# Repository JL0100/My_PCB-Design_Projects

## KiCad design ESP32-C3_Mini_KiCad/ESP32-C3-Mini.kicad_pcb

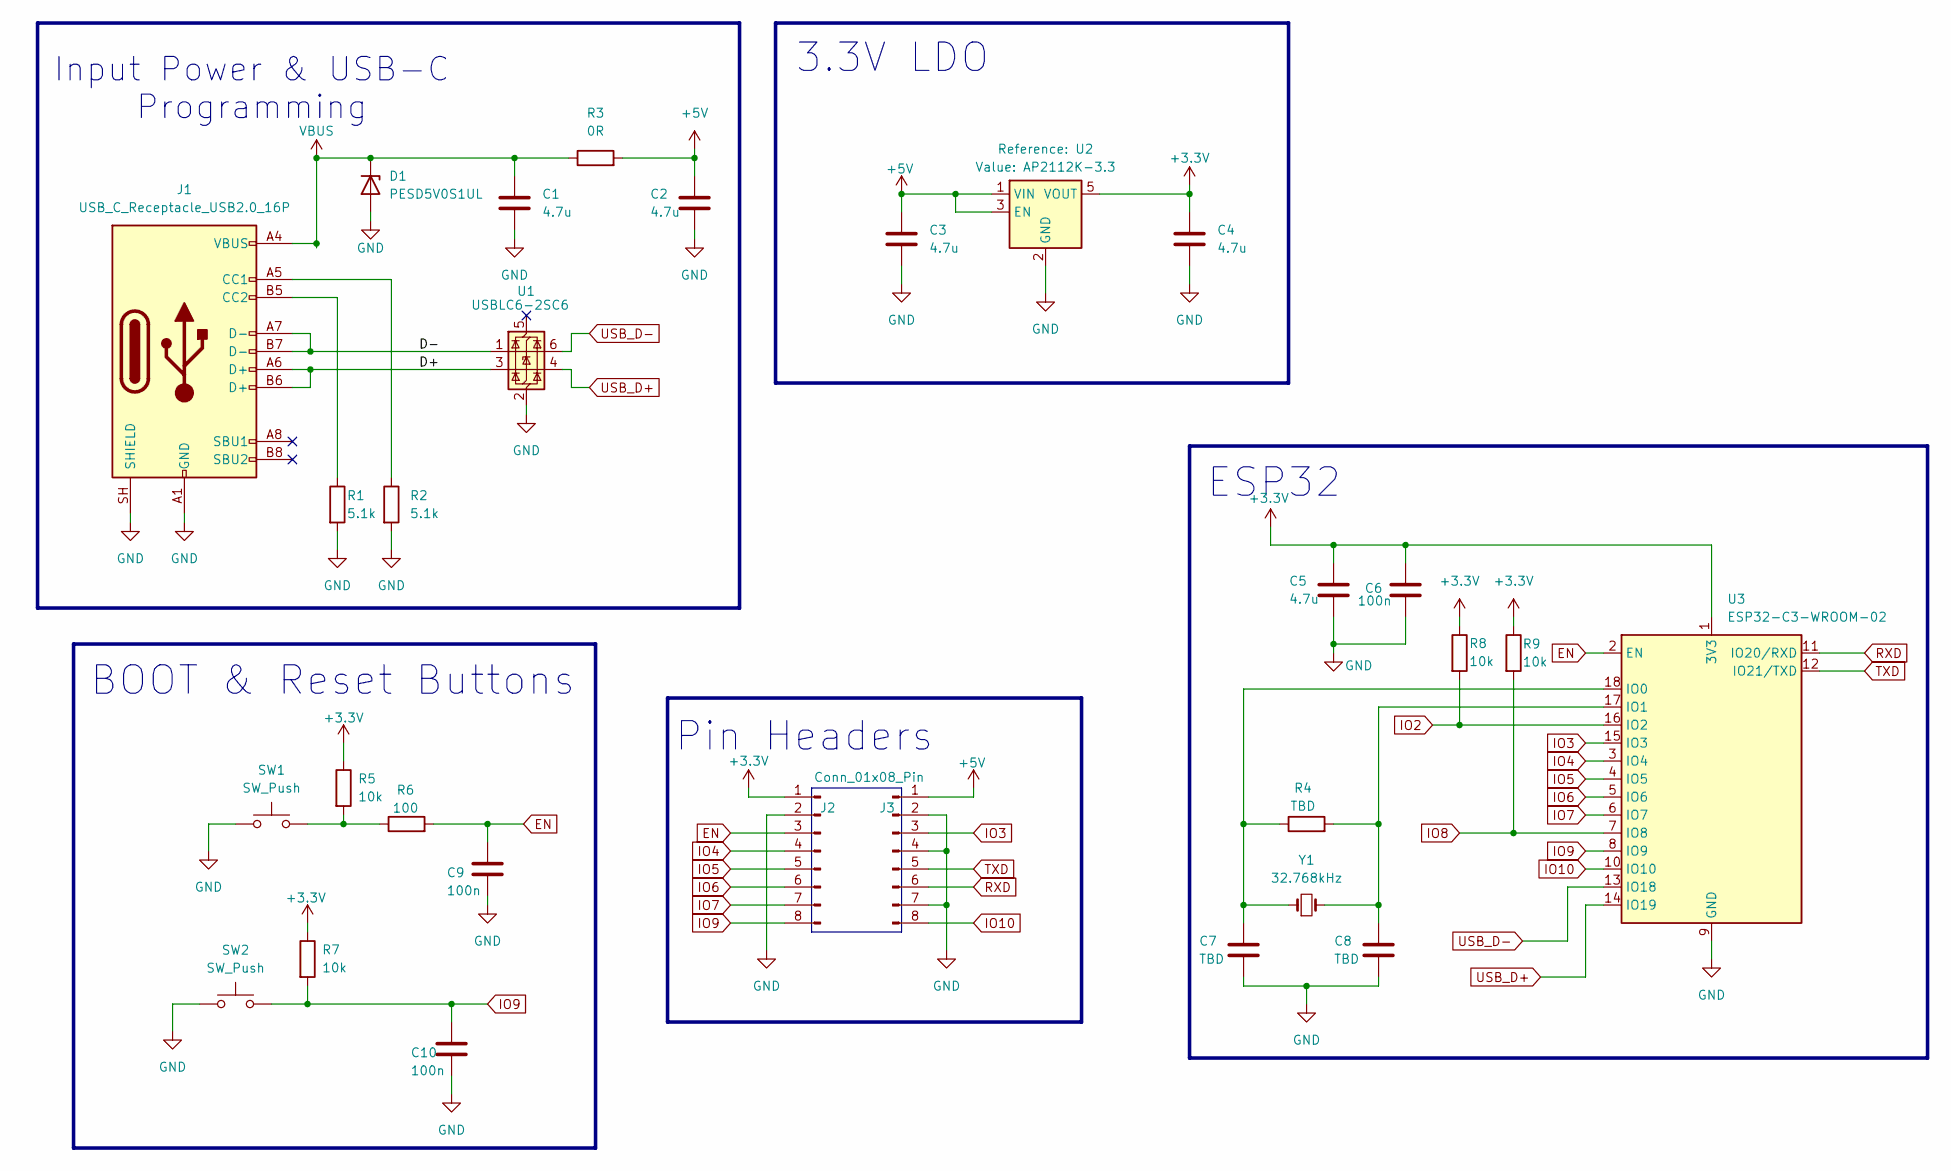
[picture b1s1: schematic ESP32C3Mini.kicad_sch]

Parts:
C1, C2, C3, C4, C5: 4.7u; C_0805_2012Metric
C6, C9, C10: 100n; C_0402_1005Metric
C7, C8: TBD; C_0402_1005Metric
D1: PESD5V0S1UL; D_SOD-882
J1: USB_C_Receptacle_USB2.0_16P; USB_C_Receptacle_G-Switch_GT-USB-7010ASV
J2, J3: Conn_01x08_Pin; PinHeader_1x08_P2.54mm_Vertical
R1, R2: 5.1k; R_0402_1005Metric
R3: 0R; R_0805_2012Metric
R4: TBD; R_0201_0603Metric
R5, R7, R8, R9: 10k; R_0402_1005Metric
R6: 100; R_0402_1005Metric
SW1, SW2: SW_Push; SW_SPST_B3U-1000P
U1: USBLC6-2SC6; SOT-23-6
U2: AP2112K-3.3; SOT23-5
U3: ESP32-C3-WROOM-02
Y1: 32.768kHz; Crystal_SMD_3215-2Pin_3.2x1.5mm

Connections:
+3.3V: C4.1, C5.1, C6.1, J2.1, R5.1, R7.1, R8.1, R9.1, U2.5 (VOUT), U3.1 (3V3)
+5V: C2.1, C3.1, J3.1, R3.2, U2.1 (VIN), U2.3 (EN)
/ESP32-C3-Mini/D+: J1.A6 (D+), J1.B6 (D+), U1.3 (I/O2)
/ESP32-C3-Mini/D-: J1.A7 (D-), J1.B7 (D-), U1.1 (I/O1)
EN: C9.1, J2.3, R6.2, U3.2 (EN)
GND: C1.2, C2.2, C3.2, C4.2, C5.2, C6.2, C7.2, C8.2, C9.2, C10.2, D1.2 (A), J1.A1 (GND), J1.A12 (GND), J1.B1 (GND), J1.B12 (GND), J1.SH (SHIELD), J2.2, J3.2, J3.4, J3.7, R1.2, R2.2, SW1.1, SW2.1, U1.2 (GND), U2.2 (GND), U3.9 (GND), U3.19 (GND); also elsewhere on the board
IO2: R8.2, U3.16 (IO2)
IO3: J3.3, U3.15 (IO3)
IO4: J2.4, U3.3 (IO4)
IO5: J2.5, U3.4 (IO5)
IO6: J2.6, U3.5 (IO6)
IO7: J2.7, U3.6 (IO7)
IO8: R9.2, U3.7 (IO8)
IO9: C10.1, J2.8, R7.2, SW2.2, U3.8 (IO9); also elsewhere on the board
IO10: J3.8, U3.10 (IO10)
unnamed: J1.A5 (CC1), R2.1
unnamed: J1.B5 (CC2), R1.1
unnamed 17: R5.2, R6.1, SW1.2; also elsewhere on the board
unnamed: C7.1, R4.1, U3.18 (IO0), Y1.1
unnamed: C8.1, R4.2, U3.17 (IO1), Y1.2
RXD: J3.6, U3.11 (IO20/RXD)
TXD: J3.5, U3.12 (IO21/TXD)
USB_D+: U1.4 (I/O2), U3.14 (IO19)
USB_D-: U1.6 (I/O1), U3.13 (IO18)
VBUS: C1.1, D1.1 (K), J1.A4 (VBUS), J1.A9 (VBUS), J1.B4 (VBUS), J1.B9 (VBUS), R3.1

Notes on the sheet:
ESP32
BOOT & Reset Buttons
Input Power & USB-C Programming
Pin Headers
3.3V LDO

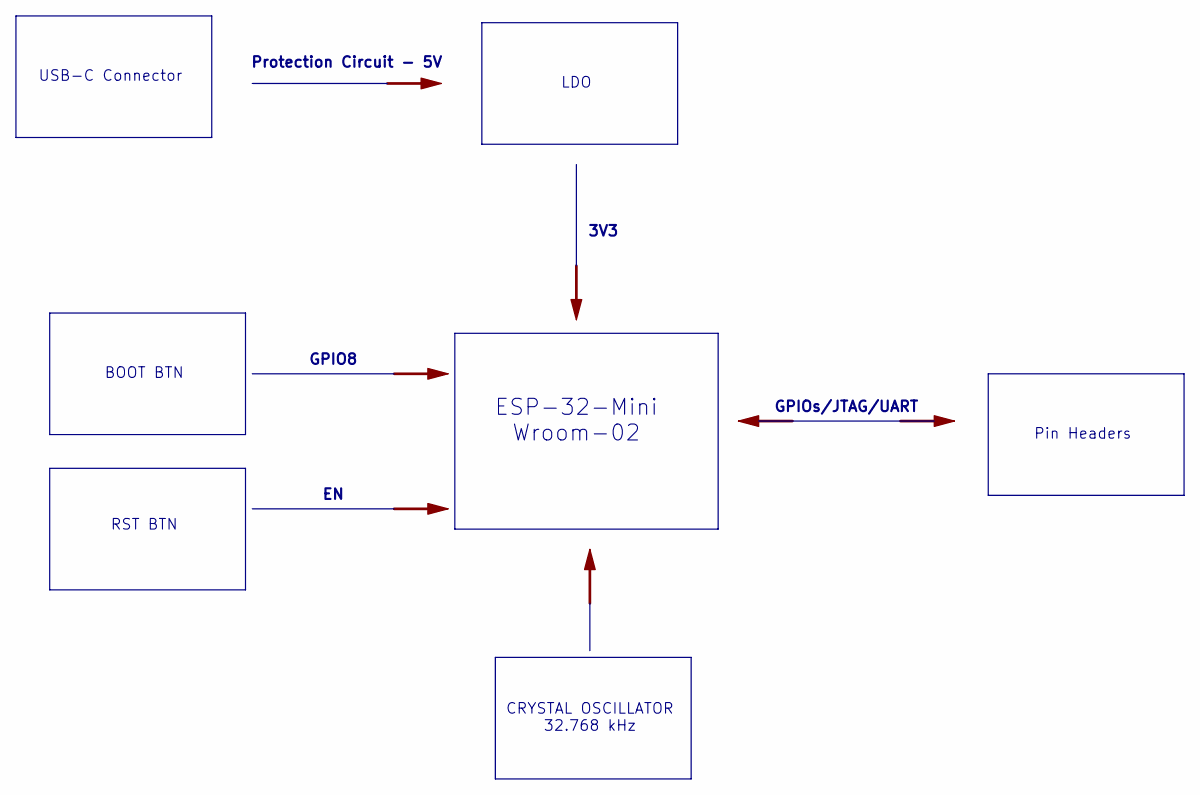
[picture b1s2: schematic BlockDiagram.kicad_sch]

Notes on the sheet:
GPIO8
Protection Circuit - 5V
GPIOs/JTAG/UART
RST BTN
USB-C Connector
Pin Headers
CRYSTAL OSCILLATOR 32.768 kHz
3V3
BOOT BTN
ESP-32-Mini Wroom-02
LDO

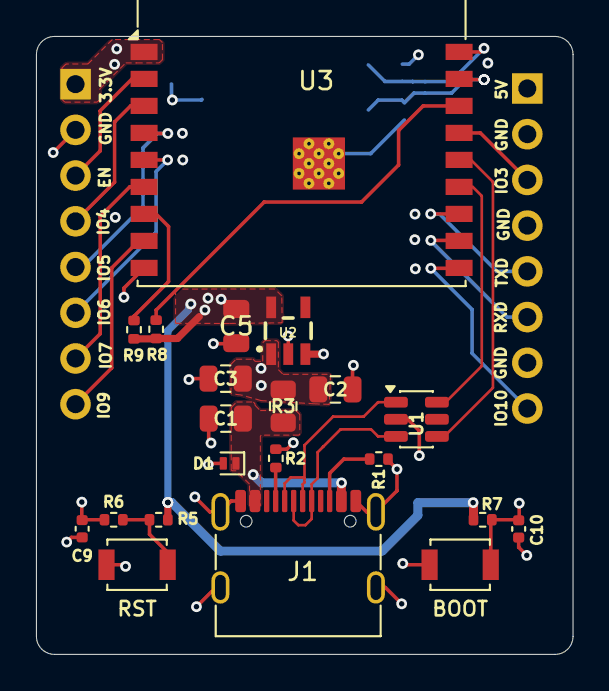
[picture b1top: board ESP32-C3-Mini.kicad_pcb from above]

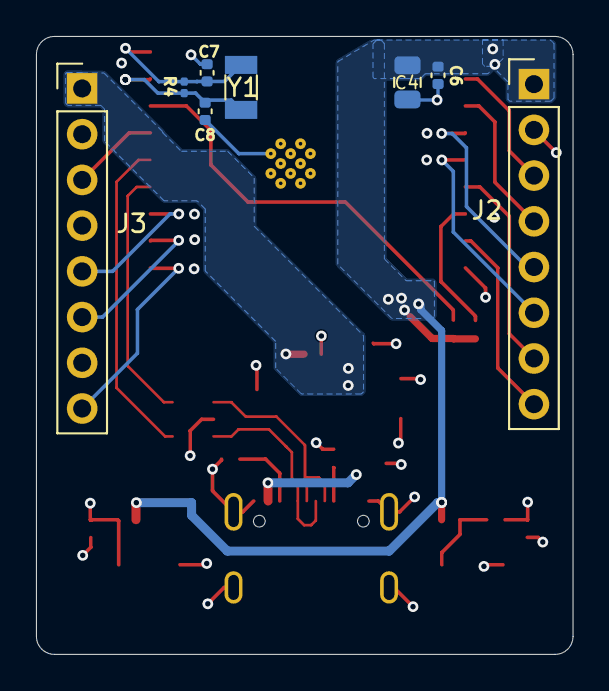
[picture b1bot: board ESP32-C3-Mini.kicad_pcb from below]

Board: 4 copper layers, 29.8 x 34.3 mm, 29 parts (8 on the bottom side), 25 nets.

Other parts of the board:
BOOT: SW_Push; SW_SPST_B3U-1000P
RST: SW_Push; SW_SPST_B3U-1000P

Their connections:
GND: BOOT.1, RST.1; also elsewhere on the board
IO9: BOOT.2; also elsewhere on the board
unnamed 17: RST.2; also elsewhere on the board
